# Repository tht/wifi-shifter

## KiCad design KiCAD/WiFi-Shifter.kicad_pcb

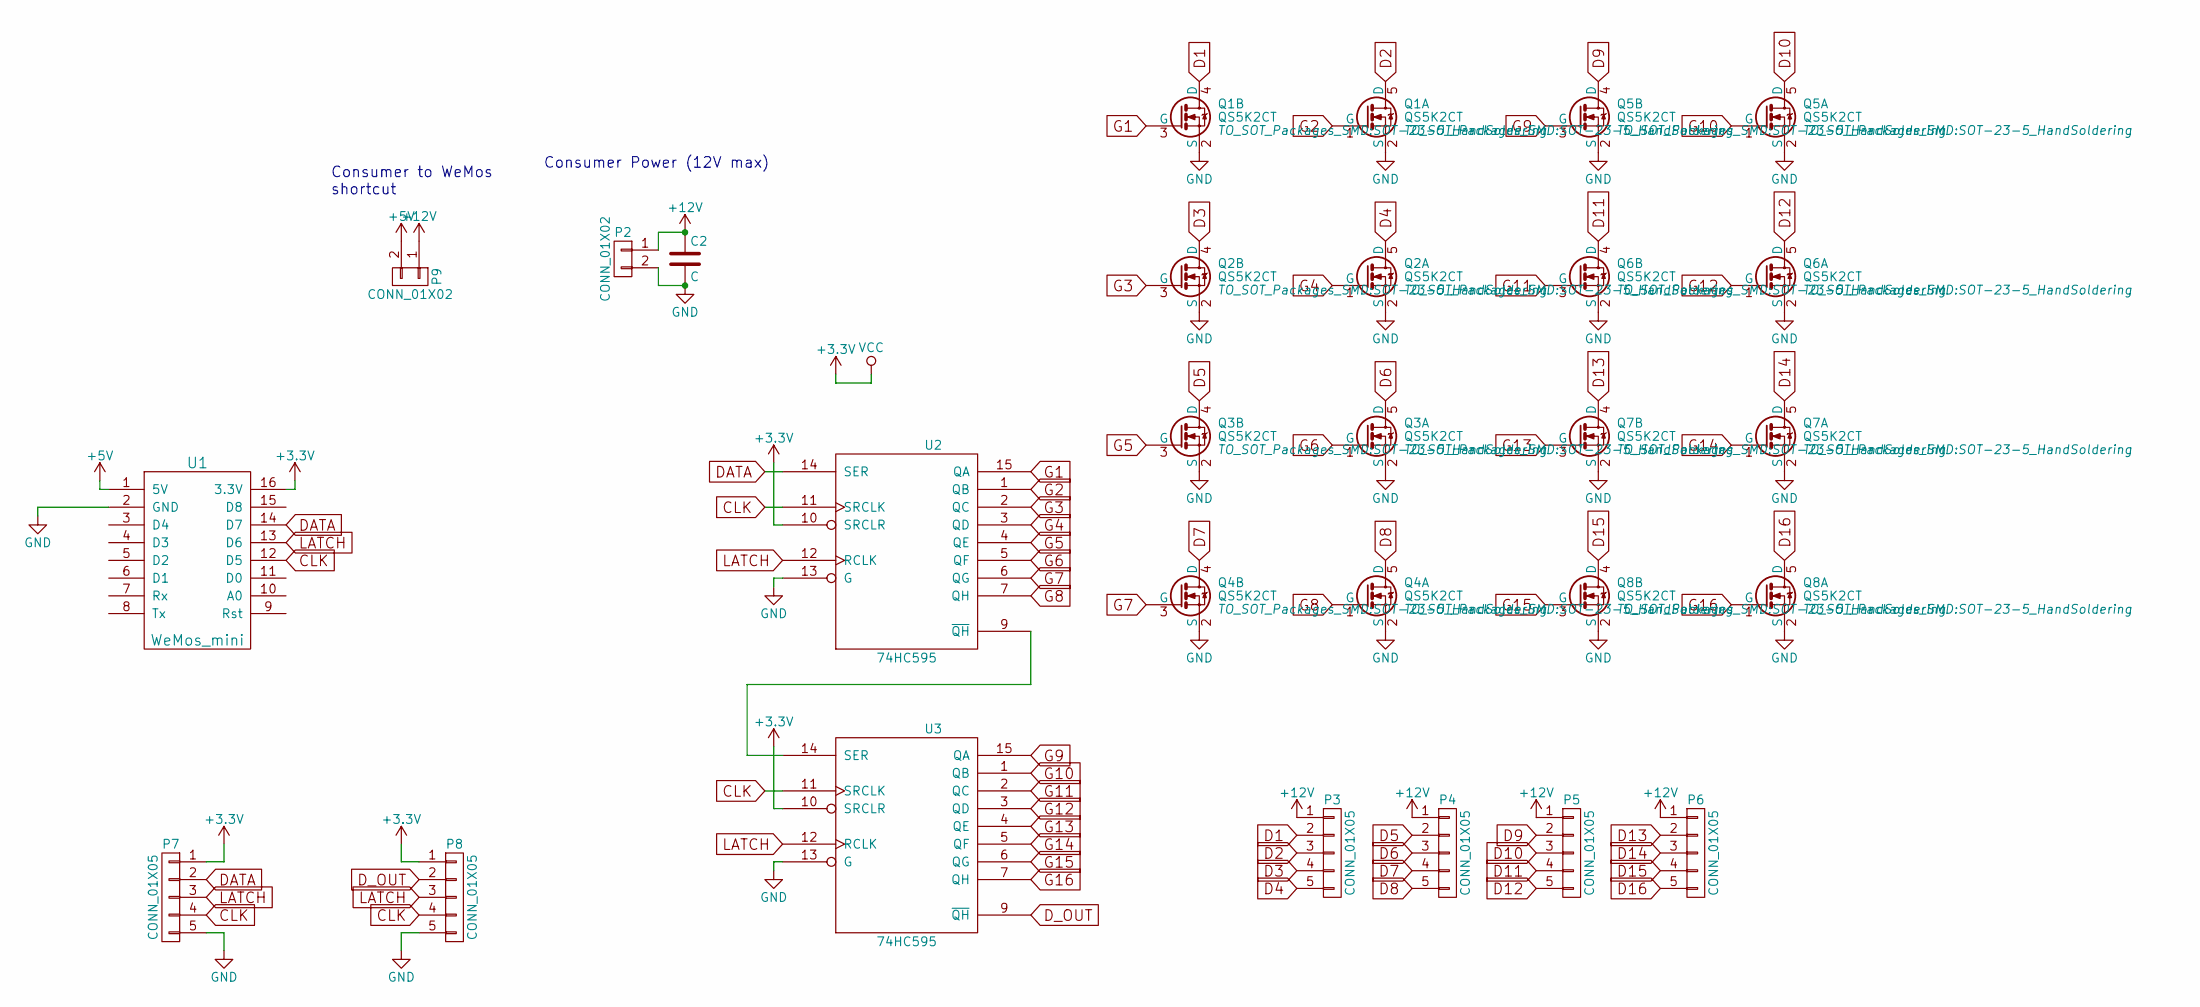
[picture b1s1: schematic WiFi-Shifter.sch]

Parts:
C2: C; CP_Radial_Tantal_D6.0mm_P2.50mm
P2: CONN_01X02; Screw_Terminal_5mm
P3, P4, P5, P6, P7, P8: CONN_01X05; JST_PH_S5B-PH-K_05x2.00mm_Angled
P9: CONN_01X02; Pin_Header_Angled_1x02_Pitch2.54mm
Q1, Q2, Q3, Q4, Q5, Q6, Q7, Q8: QS5K2CT; SOT-23-5_HandSoldering
U1: WeMos_mini; D1_mini_board
U2, U3: 74HC595; SO-16-N

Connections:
+3V3: P7.1, P8.1, U1.16 (3.3V), U2.10 (SRCLR), U2.16 (VCC), U3.10 (SRCLR), U3.16 (VCC)
+5V: P9.2, U1.1 (5V)
+12V: C2.1, P2.1, P3.1, P4.1, P5.1, P6.1, P9.1
CLK: P7.4, P8.4, U1.12 (D5), U2.11 (SRCLK), U3.11 (SRCLK)
D1: P3.2, Q1.4 (D)
D2: P3.3, Q1.5 (D)
D3: P3.4, Q2.4 (D)
D4: P3.5, Q2.5 (D)
D5: P4.2, Q3.4 (D)
D6: P4.3, Q3.5 (D)
D7: P4.4, Q4.4 (D)
D8: P4.5, Q4.5 (D)
D9: P5.2, Q5.4 (D)
D10: P5.3, Q5.5 (D)
D11: P5.4, Q6.4 (D)
D12: P5.5, Q6.5 (D)
D13: P6.2, Q7.4 (D)
D14: P6.3, Q7.5 (D)
D15: P6.4, Q8.4 (D)
D16: P6.5, Q8.5 (D)
DATA: P7.2, U1.14 (D7), U2.14 (SER)
D_OUT: P8.2, U3.9 (~QH)
G1: Q1.3 (G), U2.15 (QA)
G2: Q1.1 (G), U2.1 (QB)
G3: Q2.3 (G), U2.2 (QC)
G4: Q2.1 (G), U2.3 (QD)
G5: Q3.3 (G), U2.4 (QE)
G6: Q3.1 (G), U2.5 (QF)
G7: Q4.3 (G), U2.6 (QG)
G8: Q4.1 (G), U2.7 (QH)
G9: Q5.3 (G), U3.15 (QA)
G10: Q5.1 (G), U3.1 (QB)
G11: Q6.3 (G), U3.2 (QC)
G12: Q6.1 (G), U3.3 (QD)
G13: Q7.3 (G), U3.4 (QE)
G14: Q7.1 (G), U3.5 (QF)
G15: Q8.3 (G), U3.6 (QG)
G16: Q8.1 (G), U3.7 (QH)
GND: C2.2, P2.2, P7.5, P8.5, Q1.2 (S), Q2.2 (S), Q3.2 (S), Q4.2 (S), Q5.2 (S), Q6.2 (S), Q7.2 (S), Q8.2 (S), U1.2 (GND), U2.8 (GND), U2.13 (G), U3.8 (GND), U3.13 (G)
LATCH: P7.3, P8.3, U1.13 (D6), U2.12 (RCLK), U3.12 (RCLK)
unnamed: U2.9 (~QH), U3.14 (SER)

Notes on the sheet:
Consumer Power (12V max)
Consumer to WeMos shortcut

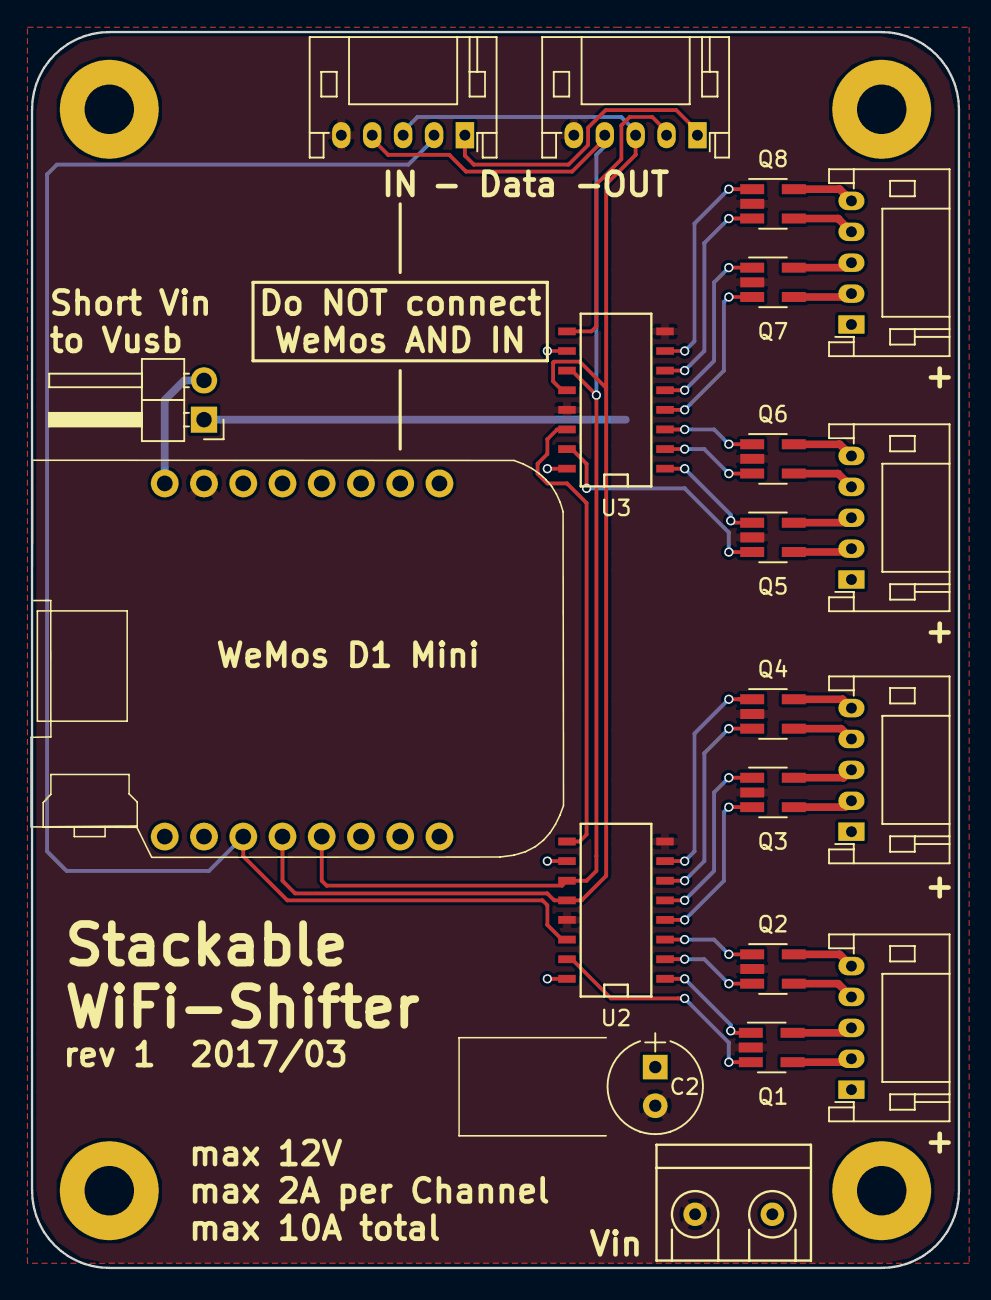
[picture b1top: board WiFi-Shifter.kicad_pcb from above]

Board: 2 copper layers, 60.0 x 80.0 mm, 20 parts (0 on the bottom side), 41 nets.

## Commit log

2017-02-26 Rev 1 as ordered
